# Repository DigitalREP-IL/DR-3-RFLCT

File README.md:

This simple breakout board is designed to fit either the TCRT5000 or the VCNT2020. A basic
implementation of the Vishay application notes is used to enable engineers to quickly evaluate the
performance of these sensors. Many very useful sensors are available in packages that are difficult to
quickly evaluate so we hope this is a meaningful addition to your toolbox.

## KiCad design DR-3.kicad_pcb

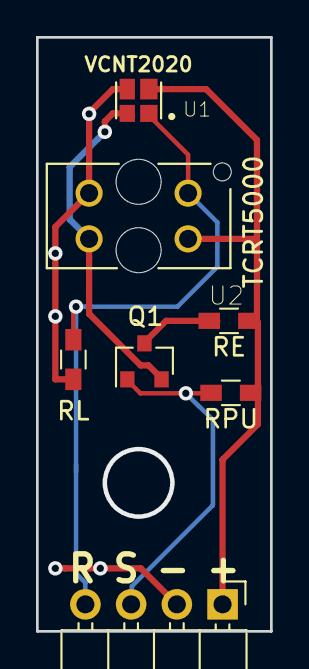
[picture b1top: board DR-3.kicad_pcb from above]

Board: 2 copper layers, 13.0 x 33.0 mm, 7 parts (0 on the bottom side), 6 nets.

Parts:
J1: Conn_01x04_Female; Pin_Header_Angled_1x04_Pitch2.54mm
Q1: 2N7002; SOT-23
RE: 220; R_0603_HandSoldering
RL: 10K; R_0603_HandSoldering
RPU: 10K; R_0603_HandSoldering
U1: VCNT2020; XDCR_VCNT2020
U2: TCRT5000; OPTO_TCRT5000

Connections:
/DRV: J1.3, Q1.1, RPU.2
/GND: J1.2, RL.2, U1.4, U2.CATH
/RCV: J1.4, RL.1, U1.1, U2.E
/VCC: J1.1, RE.1, RPU.1, U1.2, U2.COLL
unnamed: Q1.2, U1.3, U2.A
unnamed: Q1.3, RE.2

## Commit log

2024-03-14 First release.
2024-03-20 adding schematic PDF
